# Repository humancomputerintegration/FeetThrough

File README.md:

# FeetThrough: Electrotactile Foot Interface that Preserves Real-World Sensations

This is the repository for PCB schematics and code for electrical stimulation used in the "FeetThrough: Electrotactile Foot Interface that Preserves Real-World Sensations" paper (ACM UIST2023).

**Summary**: FeetThrough is an open-source device that allows you to control external applications. Its hardware is built on an ESP32 microcontroller (you can use your favorite microcontroller), a custom-built multiplexer, and an electrical stimulator (we used the medical-grade Rehastim). We provide schematics for electrodes, multiplexers, and simple Python codes for electrical stimulation. By implementing a multiplexer and preparing a stimulator, you can test electrical stimulation for feet. Regarding the details of the electrode design, please refer to our paper.

## hardware

We share schematics of multiplexer board, flexible electrodes, and connector of the electrodes.

-  multiplexer: `hardware/photorelay_multiplexer`
   - This multiplexer is mainly consisted of shift registers (74HC595) and high-voltage photorelays (TLP176GA), and half-bridge configuration is created for each electrode

- electrodes: `hardware/electrodes` and `hardware/flexible_pcb_connector`
  - to use flexible electrodes, flexible PCB connector (FPC) is needed to deliver stimulation. We designed the end of the electrodes for this connector (FH12-30S-0.5SH(55), [mouser](https://mou.sr/3Qu7VoI)).
  - `app_electrodes_top` and `app_electrodes_bottom` are the final prototype of the electrodes to deliver stimulation to the whole sole. (To use 30-ch connector, the electrodes are separated in half)
  - To test the stimulator, you do not have to create flexible PCB electrodes. You can also use gel electrodes (often used for EMS) and other types of the electrodes if they are able to connect to the multiplexer

- stimulator (current source)
  - While we used the medical-grade RehaStim, you can use other electrical stimulators such as [RehaMove](https://github.com/humancomputerintegration/rehamove-integration-lib), [openEMSstim](https://github.com/PedroLopes/openEMSstim), [Electro-Tactile Display Kit for Fingertip (Kajimoto 2021)](https://ieeexplore.ieee.org/abstract/document/9517192).
  - connect the current source to `V+` and `V-` in the circuit.
  - We show another example of implementation with [a stimulator of Kajimoto 2021](https://ieeexplore.ieee.org/abstract/document/9517192)
  - 

## source code

We share software code to stimulate multiple electrodes. To use the code, you have to prepare your stimulator and implement client for it. This code was developed for Windows 11

- client: `code/simple_stimulation`
  - `main.py`: simple controller of electrical stimulation
  - `custom_serial.py`: client for microcontroller of multiplexer
  - `photo_relay_switching.py`: Each channel of the multiplexer has three states (HIGH (V+), LOW (V-), OPEN (not connected)). This program manages and changes the states of multiplexer in software
  - `electro_stimulator.py`: client for electrical stimulator. This program controlls stimulation frequency and synchronize the timing between multiplexing and stimulator. 

in `electro_stimulator.py`, please change the code to use your stimulator

```python:electro_stimulator.py
# client for electrical stimulator ----- 
# NEED IMPLEMENTATION
client = ## please implement a client for your stimulator
## ------------------ 
```

```python:electro_stimulator.py
# --- send one pulse ---
# NEED IMPLEMENTATION
# client.write()
# --------
```

## how to use

- upload `arduino/multiplexer_esp32` to a microcontroller (ESP32 DevKitC 32E, [mouser](https://mou.sr/3GRjfHH)) through Arduino Software
  - before running the code, check and change `baudrate` and `com port` in `custom_serial.py`
- connect multiplexer and electrical stimulator to your PC
- run `main.py` in `code/simple_stimulation`

## contact

For any questions about this repository, please contact Keigo Ushiyama (ushiyama@kaji-lab.jp)

## citation

When using or building upon this work in an academic publication, please consider citing as follows:

Keigo Ushiyama and Pedro Lopes. 2023. FeetThrough: Electrotactile Foot Interface that Preserves Real-World Sensations. In Proceedings of the 36th Annual ACM Symposium on User Interface Software and Technology (UIST '23). Association for Computing Machinery, New York, NY, USA, Article 10, 1–11. https://doi.org/10.1145/3586183.3606808

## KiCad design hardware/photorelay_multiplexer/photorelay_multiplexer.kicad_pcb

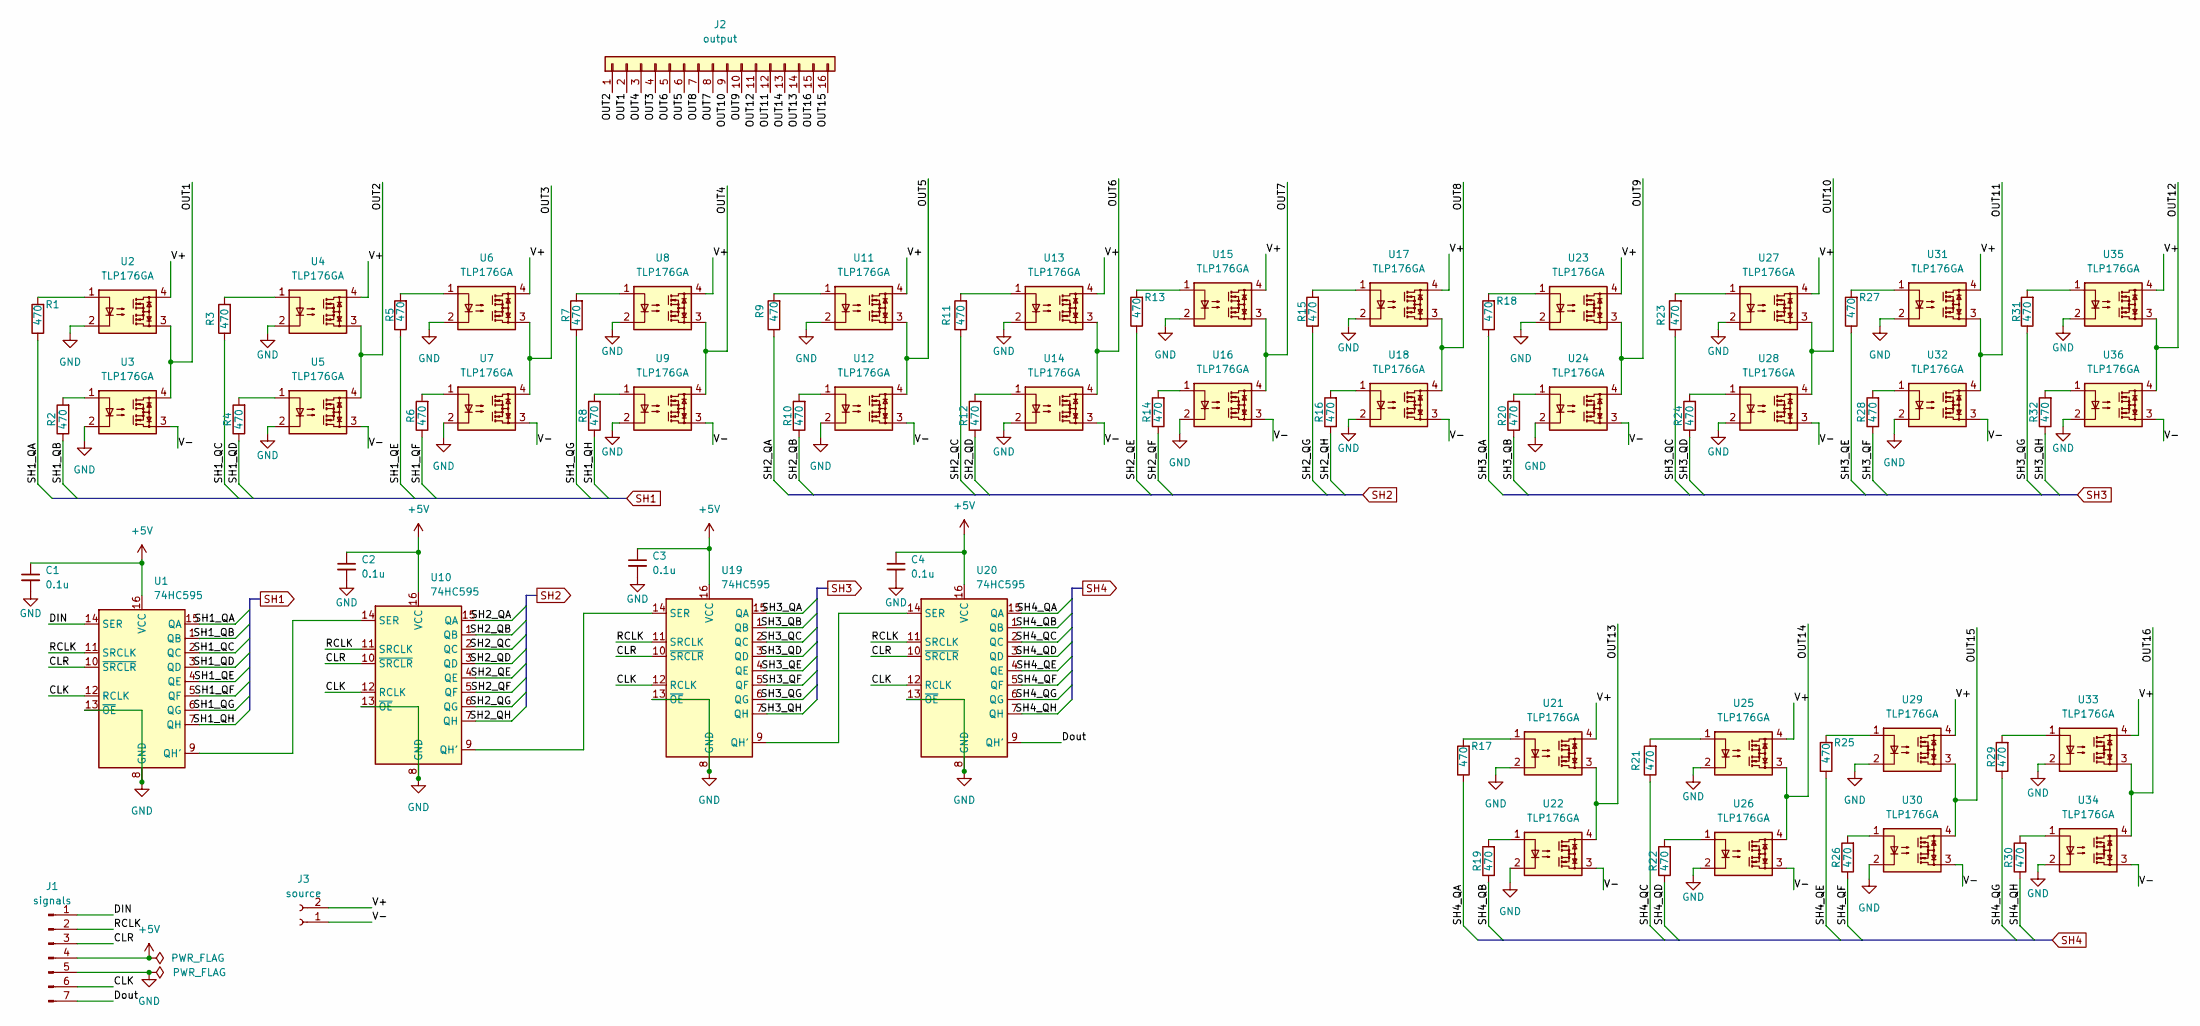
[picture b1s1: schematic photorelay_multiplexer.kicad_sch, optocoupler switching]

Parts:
C1, C2, C3, C4: 0.1u; C_0603_1608Metric
J1: signals; PinSocket_1x07_P2.54mm_Vertical
J2: output; PinSocket_2x08_P2.54mm_Vertical
J3: source; PinSocket_1x02_P2.54mm_Vertical
R1, R2, R3, R4, R5, R6, R7, R8, R9, R10, R11, R12, R13, R14, R15, R16, R17, R18, R19, R20, R21, R22, R23, R24, R25, R26, R27, R28, R29, R30, R31, R32: 470; R_0603_1608Metric
U1, U10, U19, U20: 74HC595; TSSOP-16_4.4x5mm_P0.65mm; LCSC C273642
U2: TLP176GA; LCSC C516859
U3, U4, U5, U6, U7, U8, U9, U11, U12, U13, U14, U15, U16, U17, U18, U21, U22, U23, U24, U25, U26, U27, U28, U29, U30, U31, U32, U33, U34, U35, U36: TLP176GA

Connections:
+5V: C1.1, C2.1, C3.1, C4.1, J1.4, U1.16 (VCC), U10.16 (VCC), U19.16 (VCC), U20.16 (VCC)
/CLK: J1.6, U1.12 (RCLK), U10.12 (RCLK), U19.12 (RCLK), U20.12 (RCLK)
/CLR: J1.3, U1.10 (~SRCLR), U10.10 (~SRCLR), U19.10 (~SRCLR), U20.10 (~SRCLR)
/DIN: J1.1, U1.14 (SER)
/Dout: J1.7, U20.9 (QH')
/OUT1: J2.2, U2.3, U3.4
/OUT2: J2.1, U4.3, U5.4
/OUT3: J2.4, U6.3, U7.4
/OUT4: J2.3, U8.3, U9.4
/OUT5: J2.6, U11.3, U12.4
/OUT6: J2.5, U13.3, U14.4
/OUT7: J2.8, U15.3, U16.4
/OUT8: J2.7, U17.3, U18.4
/OUT9: J2.10, U23.3, U24.4
/OUT10: J2.9, U27.3, U28.4
/OUT11: J2.12, U31.3, U32.4
/OUT12: J2.11, U35.3, U36.4
/OUT13: J2.14, U21.3, U22.4
/OUT14: J2.13, U25.3, U26.4
/OUT15: J2.16, U29.3, U30.4
/OUT16: J2.15, U33.3, U34.4
/RCLK: J1.2, U1.11 (SRCLK), U10.11 (SRCLK), U19.11 (SRCLK), U20.11 (SRCLK)
/SH1_QA: R1.1, U1.15 (QA)
/SH1_QB: R2.1, U1.1 (QB)
/SH1_QC: R3.1, U1.2 (QC)
/SH1_QD: R4.1, U1.3 (QD)
/SH1_QE: R5.1, U1.4 (QE)
/SH1_QF: R6.1, U1.5 (QF)
/SH1_QG: R7.1, U1.6 (QG)
/SH1_QH: R8.1, U1.7 (QH)
/SH2_QA: R9.1, U10.15 (QA)
/SH2_QB: R10.1, U10.1 (QB)
/SH2_QC: R11.1, U10.2 (QC)
/SH2_QD: R12.1, U10.3 (QD)
/SH2_QE: R13.1, U10.4 (QE)
/SH2_QF: R14.1, U10.5 (QF)
/SH2_QG: R15.1, U10.6 (QG)
/SH2_QH: R16.1, U10.7 (QH)
/SH3_QA: R18.1, U19.15 (QA)
/SH3_QB: R20.1, U19.1 (QB)
/SH3_QC: R23.1, U19.2 (QC)
/SH3_QD: R24.1, U19.3 (QD)
/SH3_QE: R27.1, U19.4 (QE)
/SH3_QF: R28.1, U19.5 (QF)
/SH3_QG: R31.1, U19.6 (QG)
/SH3_QH: R32.1, U19.7 (QH)
/SH4_QA: R17.1, U20.15 (QA)
/SH4_QB: R19.1, U20.1 (QB)
/SH4_QC: R21.1, U20.2 (QC)
/SH4_QD: R22.1, U20.3 (QD)
/SH4_QE: R25.1, U20.4 (QE)
/SH4_QF: R26.1, U20.5 (QF)
/SH4_QG: R29.1, U20.6 (QG)
/SH4_QH: R30.1, U20.7 (QH)
/V+: J3.2, U2.4, U4.4, U6.4, U8.4, U11.4, U13.4, U15.4, U17.4, U21.4, U23.4, U25.4, U27.4, U29.4, U31.4, U33.4, U35.4
/V-: J3.1, U3.3, U5.3, U7.3, U9.3, U12.3, U14.3, U16.3, U18.3, U22.3, U24.3, U26.3, U28.3, U30.3, U32.3, U34.3, U36.3
GND: C1.2, C2.2, C3.2, C4.2, J1.5, U1.8 (GND), U1.13 (~OE), U2.2, U3.2, U4.2, U5.2, U6.2, U7.2, U8.2, U9.2, U10.8 (GND), U10.13 (~OE), U11.2, U12.2, U13.2, U14.2, U15.2, U16.2, U17.2, U18.2, U19.8 (GND), U19.13 (~OE), U20.8 (GND), U20.13 (~OE), U21.2, U22.2, U23.2, U24.2, U25.2, U26.2, U27.2, U28.2, U29.2, U30.2, U31.2, U32.2, U33.2, U34.2, U35.2, U36.2
unnamed: R1.2, U2.1
unnamed: R2.2, U3.1
unnamed: R3.2, U4.1
unnamed: R4.2, U5.1
unnamed: R5.2, U6.1
unnamed: R6.2, U7.1
unnamed: R7.2, U8.1
unnamed: R8.2, U9.1
unnamed: R9.2, U11.1
unnamed: R10.2, U12.1
unnamed: R11.2, U13.1
unnamed: R12.2, U14.1
unnamed: R13.2, U15.1
unnamed: R14.2, U16.1
unnamed: R15.2, U17.1
unnamed: R16.2, U18.1
unnamed: R17.2, U21.1
unnamed: R18.2, U23.1
unnamed: R19.2, U22.1
unnamed: R20.2, U24.1
unnamed: R21.2, U25.1
unnamed: R22.2, U26.1
unnamed: R23.2, U27.1
unnamed: R24.2, U28.1
unnamed: R25.2, U29.1
unnamed: R26.2, U30.1
unnamed: R27.2, U31.1
unnamed: R28.2, U32.1
unnamed: R29.2, U33.1
unnamed: R30.2, U34.1
unnamed: R31.2, U35.1
unnamed: R32.2, U36.1
unnamed: U1.9 (QH'), U10.14 (SER)
unnamed: U10.9 (QH'), U19.14 (SER)
unnamed: U19.9 (QH'), U20.14 (SER)

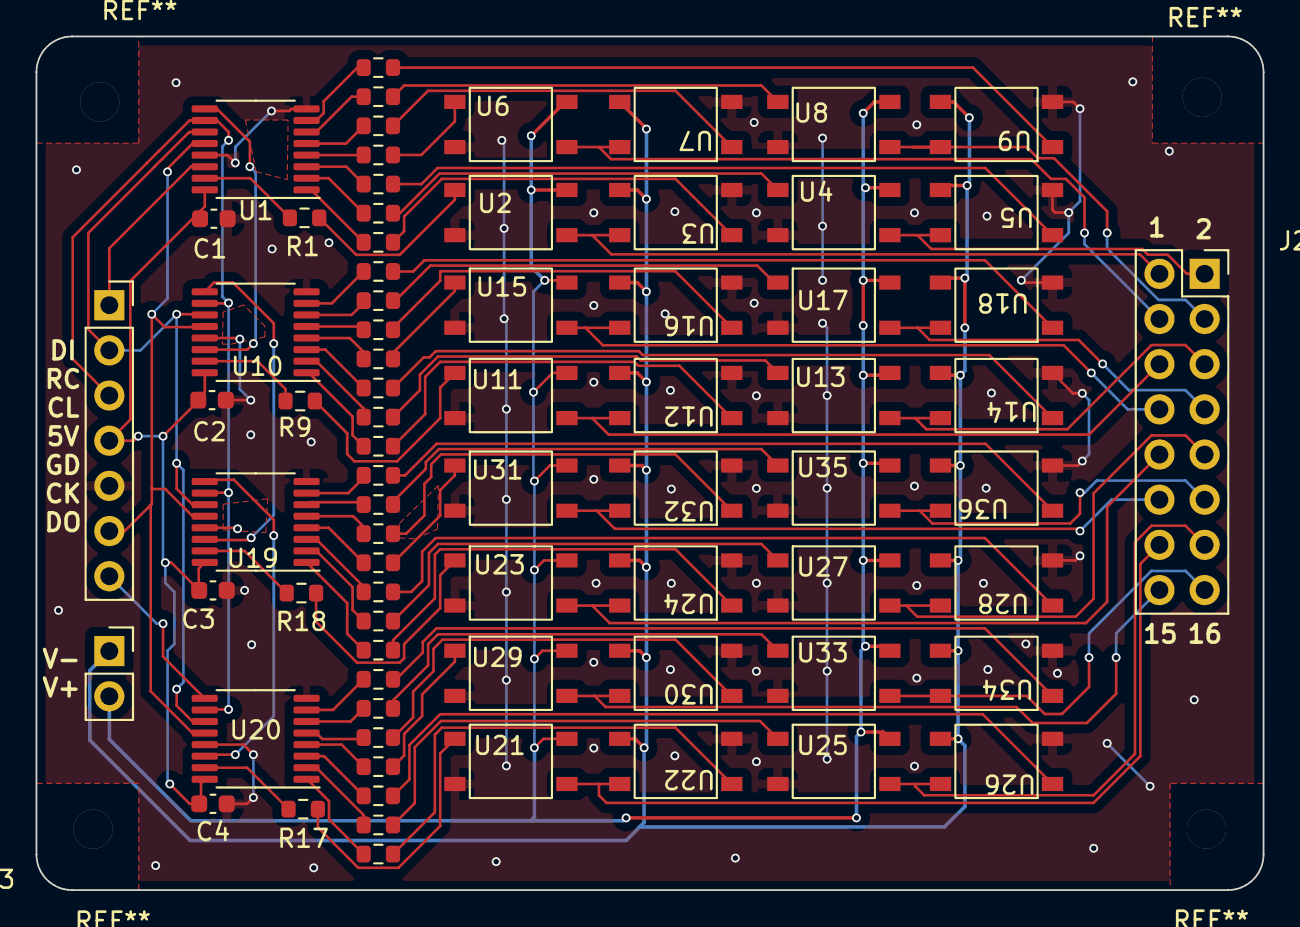
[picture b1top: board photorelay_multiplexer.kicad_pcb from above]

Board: 2 copper layers, 69.0 x 48.0 mm, 75 parts (0 on the bottom side), 92 nets.

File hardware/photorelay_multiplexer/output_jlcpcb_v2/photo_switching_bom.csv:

Comment,Designator,Footprint,JLCPCB Part #
0.1u,"C1,C2,C3,C4",Capacitor_SMD:C_0603_1608Metric,C14663
signals,J1,Connector_PinSocket_2.54mm:PinSocket_1x07_P2.54mm_Vertical,C2932672
output,J2,Connector_PinSocket_2.54mm:PinSocket_2x08_P2.54mm_Vertical,C239348
source,J3,Connector_PinSocket_2.54mm:PinSocket_1x02_P2.54mm_Vertical,C2905414
470,"R1,R2,R3,R4,R5,R6,R7,R8,R9,R10,R11,R12,R13,R14,R15,R16,R17,R18,R19,R20,R21,R22,R23,R24,R25,R26,R27,R28,R29,R30,R31,R32",Resistor_SMD:R_0603_1608Metric,C23179
74HC595,"U1,U10,U19,U20",Package_SO:TSSOP-16_4.4x5mm_P0.65mm,C273642
TLP176GA,"U2,U3,U4,U5,U6,U7,U8,U9,U11,U12,U13,U14,U15,U16,U17,U18,U21,U22,U23,U24,U25,U26,U27,U28,U29,U30,U31,U32,U33,U34,U35,U36",keigo_custom_footprint:TLP176GA,C516859

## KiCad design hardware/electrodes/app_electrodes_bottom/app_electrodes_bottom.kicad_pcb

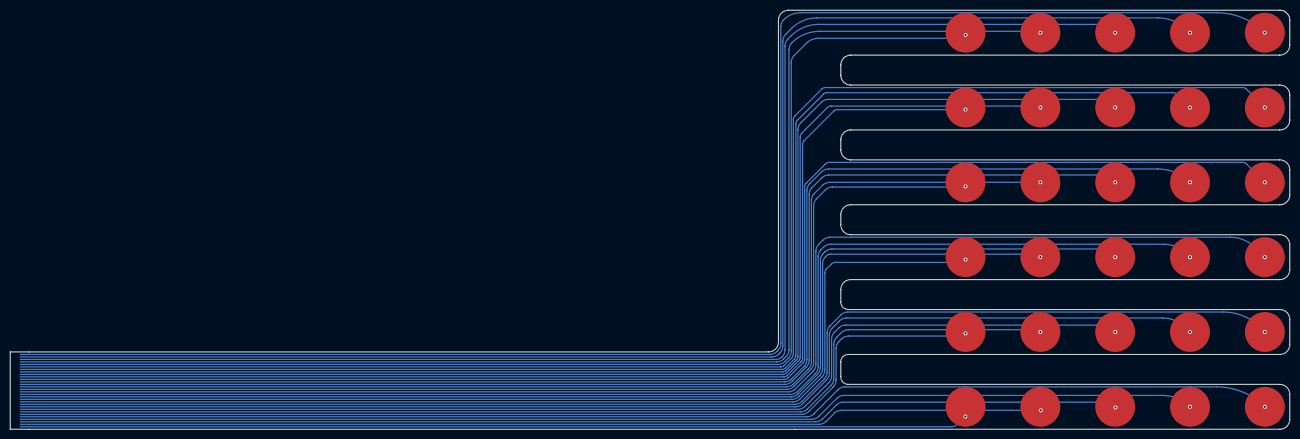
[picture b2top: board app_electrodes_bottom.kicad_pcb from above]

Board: 2 copper layers, 256.5 x 84.0 mm, 31 parts (1 on the bottom side), 30 nets.

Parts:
J2, J3, J4, J5, J6, J8, J9, J10, J11, J12, J14, J15, J17, J18, J19, J21, J22, J23, J24, J25, J27, J28, J29, J30, J31, J32, J33, J34, J35, J36: electrode_pad; electrode_pad_smd
J16: flex_terminal_11; flex_hirose_30

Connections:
unnamed: J6.1, J16.1
unnamed: J8.10, J16.10
unnamed: J16.11, J19.11
unnamed: J16.12, J18.12
unnamed: J16.13, J17.13
unnamed: J15.14, J16.14
unnamed: J14.15, J16.15
unnamed: J5.2, J16.2
unnamed: J4.3, J16.3
unnamed: J3.4, J16.4
unnamed: J2.5, J16.5
unnamed: J12.6, J16.6
unnamed: J11.7, J16.7
unnamed: J10.8, J16.8
unnamed: J9.9, J16.9
unnamed: J16.16, J25.16
unnamed: J16.17, J24.17
unnamed: J16.18, J23.18
unnamed: J16.19, J22.19
unnamed: J16.20, J21.20
unnamed: J16.21, J31.21
unnamed: J16.22, J30.22
unnamed: J16.23, J29.23
unnamed: J16.24, J28.24
unnamed: J16.25, J27.25
unnamed: J16.26, J36.26
unnamed: J16.27, J35.27
unnamed: J16.28, J34.28
unnamed: J16.29, J33.29
unnamed: J16.30, J32.30

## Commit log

2023-11-09 uploading sources for FeetThrough
2023-11-09 minor change
